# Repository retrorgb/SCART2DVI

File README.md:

# SCART2DVI
Please refer to the [SCART2DVI](https://www.retrorgb.com/scart2dvi.html) page on RetroRGB for more information.

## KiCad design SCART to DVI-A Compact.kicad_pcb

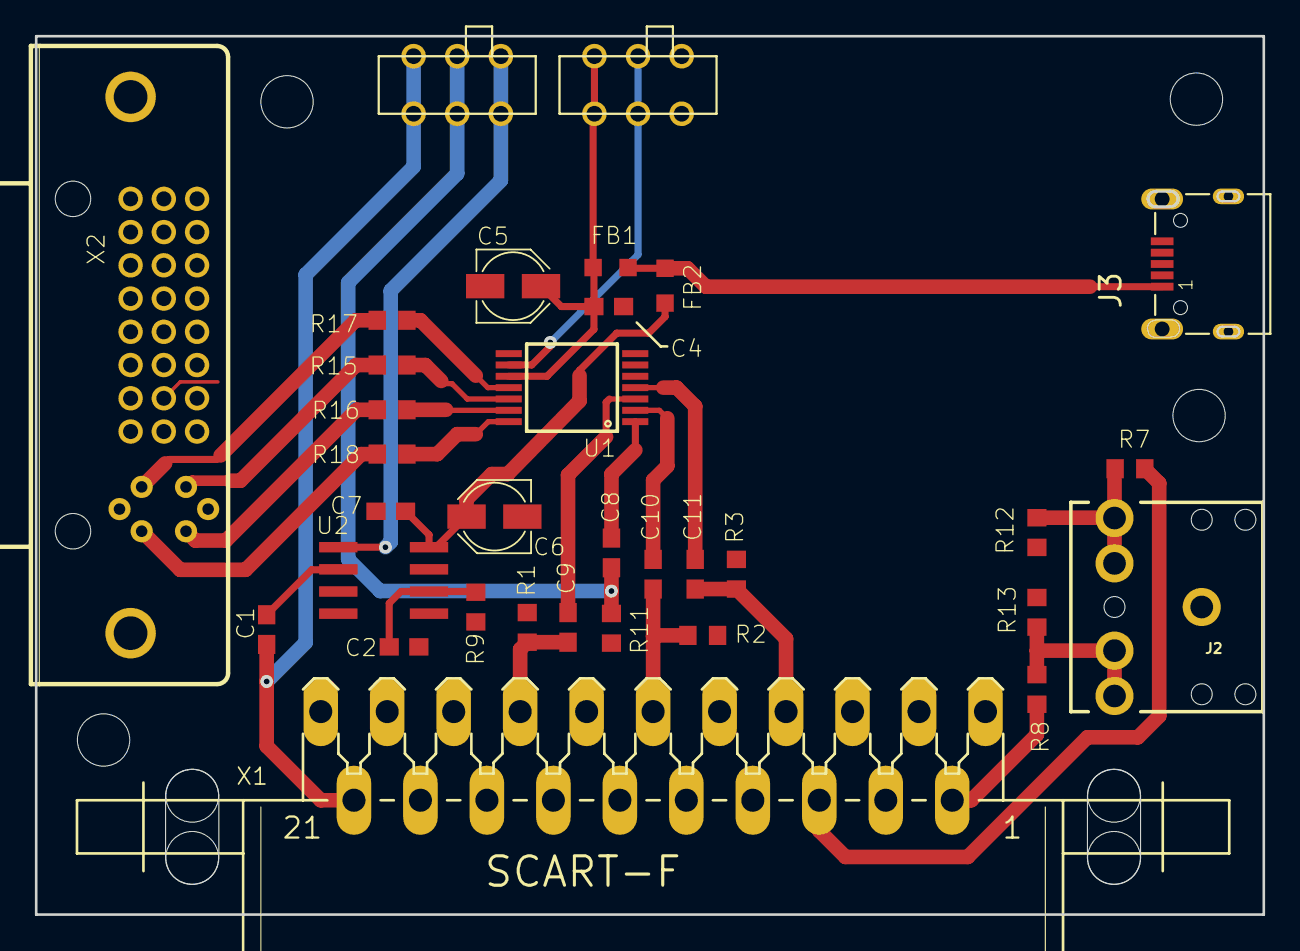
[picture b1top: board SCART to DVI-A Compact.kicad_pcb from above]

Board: 2 copper layers, 70.4 x 50.3 mm, 37 parts (0 on the bottom side), 29 nets.

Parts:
@HOLE0, @HOLE1, @HOLE2, @HOLE3: (no value)
C1, C2, C4, C7, C8, C9, C10, C11: 100nF; C0603
C5, C6: 100uF 6.3V; PANASONIC_B
FB1, FB2: FB_330R; L2012C
J2: AUDIO_JACK_3.5MM_KIT; AUDIO-JACK-KIT
J3: 629105150521
R1, R2, R3, R11, R15, R16, R17, R18: 75R; R0603
R7, R8, R12, R13: 100R; R0603
R9: 680K; R0603
U1: THS7374; SO14W
U2: LM1881; SO08
U$2, U$3: JS202011
X1: SCART-F
X2: DVI-I-R

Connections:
+5V: FB1.2, FB2.2, J3.1
/CSYNC_IN: C8.2, R11.2, U$2.2, U$2.5
/DVI_OUT_B: R17.1, X2.C3
/DVI_OUT_G: R16.1, X2.C2
/DVI_OUT_HSYNC: R18.1, X2.C4
/DVI_OUT_R: R15.1, X2.C1
/LM_OUT_CSYNC: U2.1, U$2.1, U$2.4
/OUT_AUD_L: J2.TIP, J2.TSH, R7.1, R12.1
/OUT_AUD_R: J2.RING, J2.RSH, R8.1, R13.1
/SCART_IN_AUD_L: R7.2, X1.6
/SCART_IN_AUD_R: R8.2, X1.2
/SCART_IN_B: C11.2, R3.2, X1.7
/SCART_IN_CVID: C1.1, U$2.3, U$2.6, X1.20
/SCART_IN_G: C10.2, R2.2, X1.11
/SCART_IN_R: C9.2, R1.2, X1.15
/THS_5V: C4.1, C5.+, FB1.1, U1.10, U$3.3, U$3.6
/THS_FILTER: U1.9, U$3.2, U$3.5
/THS_IN_B: C11.1, U1.4
/THS_IN_CSYNC: C8.1, U1.1
/THS_IN_G: C10.1, U1.2
/THS_IN_R: C9.1, U1.3
GND: C2.2, C4.2, C5.-, C6.-, C7.2, J2.SLEEVE, J3.5, J3.SHELL, J3.SHELL1, J3.SHELL2, J3.SHELL3, R1.1, R2.1, R3.1, R9.2, R11.1, R12.2, R13.2, U1.5, U1.6, U2.4, U$3.1, U$3.4, X1.4, X1.5, X1.14, X1.17, X1.18, X1.21, X2.3, X2.11, X2.15, X2.19, X2.C5, X2.GND@1, X2.GND@2
unnamed: C1.2, U2.2
unnamed: C2.1, R9.1, U2.6
unnamed: C6.+, C7.1, FB2.1, U2.8
unnamed: R15.2, U1.12
unnamed: R16.2, U1.13
unnamed: R17.2, U1.11
unnamed: R18.2, U1.14

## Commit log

2019-06-13 Eagle Version
    Initial Eagle version of the board.
2019-06-13 KiCAD Version
    Converted to KiCAD
2019-06-13 Create license
